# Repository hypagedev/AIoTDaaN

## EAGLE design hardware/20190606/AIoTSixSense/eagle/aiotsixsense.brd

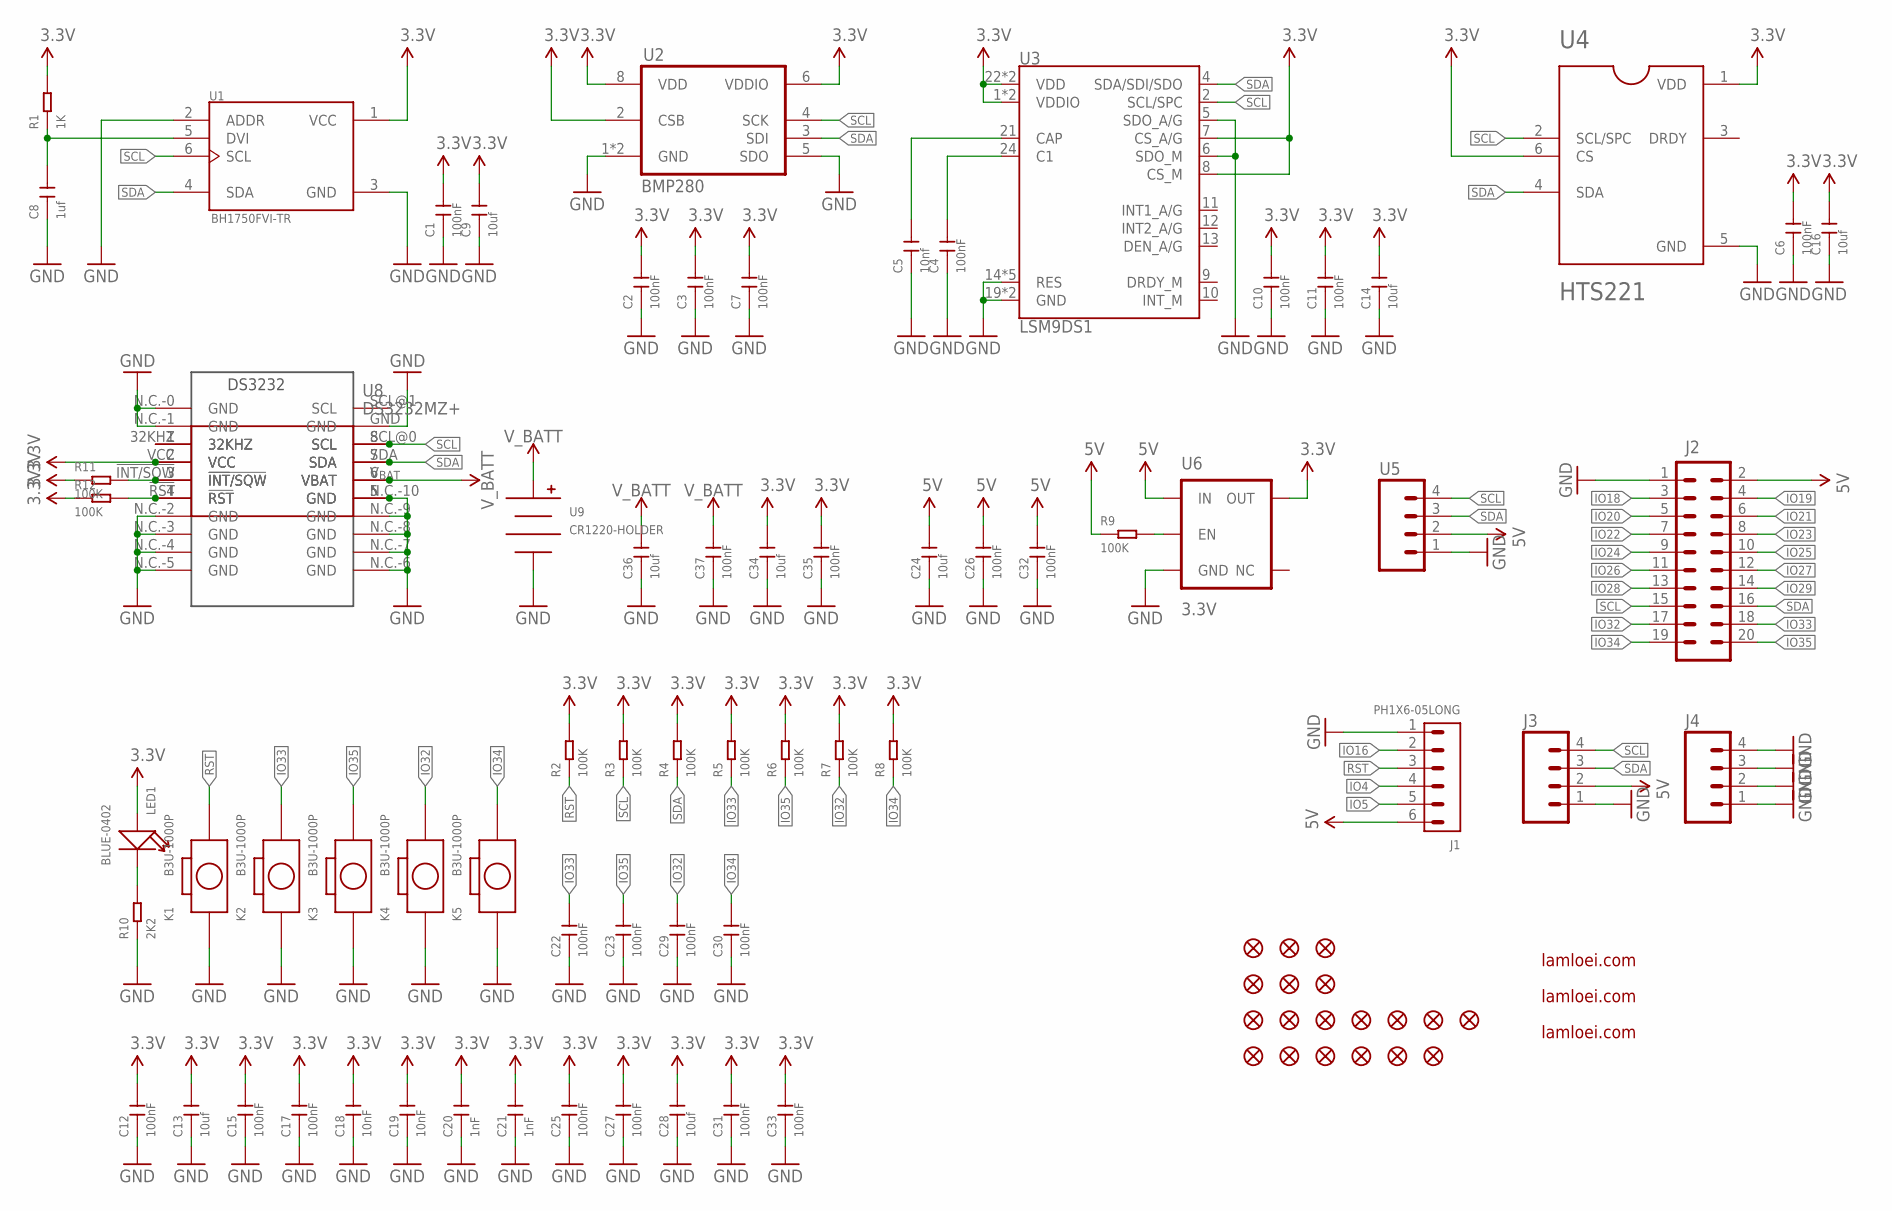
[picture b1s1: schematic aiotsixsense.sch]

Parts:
C1, C2, C3, C4, C6, C7, C10, C11, C12, C15, C17, C22, C23, C25, C26, C27, C29, C30, C31, C32, C33, C35, C37: 100nF; C0402
C5: 10nf; C0402
C8: 1uf; C0402
C9, C13, C14, C16, C24, C28, C34, C36: 10uf; C0805
C18, C19: 10nF; C0402
C20, C21: 1nF; C0402
J1: PH1X6-05LONG; PHL005-1-6
J2: M10X2; 2X10
J3, J4: M04SMD_RA_FEMALE; 1X04_SMD_RA_FEMALE
K1, K2, K3, K4, K5: B3U-1000P; SW2-SMD-3.0X2.5X1.2+0.4MM
LED1: BLUE-0402; LED-0402
R1: 1K; R0402
R2, R3, R4, R5, R6, R7, R8, R9, R11, R12: 100K; R0402
R10: 2K2; R0402
U1: BH1750FVI-TR; SOTFL50P300X75-6N
U2: BMP280
U3: LSM9DS1; LGA-24-3.5X3
U4: HTS221; LGA6R75P3X2_200X200X90
U5: M04LONGPADS; 1X04_LONGPADS
U6: 3.3V; SOT23-5
U7: DS3232; SO20-2
U8: DS3232MZ+; SOIC127P600X175-8N
U9: CR1220-HOLDER; HARWIN-CR1220
ZFCB1, ZFCB2, ZFCB3: FIDUCIAL1X2; FIDUCIAL-1X2
ZFCT1, ZFCT2, ZFCT3: FIDUCIAL1X2; FIDUCIAL-1X2
ZFDB1, ZFDB2, ZFDB3, ZFDB4, ZFDB5, ZFDB6: FIDUCIAL1X2; FIDUCIAL-1X2
ZFDT1, ZFDT2, ZFDT3, ZFDT4, ZFDT5, ZFDT6, ZFDT7: FIDUCIAL1X2; FIDUCIAL-1X2
ZL1: LAMLOEI_BIGLOGO
ZL2, ZL3: LAMLEOI_LOGO_3

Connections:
3.3V: C1.2, C2.2, C3.2, C6.2, C7.2, C9.2, C10.2, C11.2, C12.2, C13.2, C14.2, C15.2, C16.2, C17.2, C18.2, C19.2, C20.2, C21.2, C25.2, C27.2, C28.2, C31.2, C33.2, C34.2, C35.2, LED1.+, R1.2, R2.2, R3.2, R4.2, R5.2, R6.2, R7.2, R8.2, R11.1, R12.1, U1.1 (VCC), U2.2 (CSB), U2.6 (VDDIO), U2.8 (VDD), U3.1 (VDDIO), U3.3 (VDDIO), U3.7 (CS_A/G), U3.8 (CS_M), U3.22 (VDD), U3.23 (VDD), U4.1 (VDD), U4.6 (CS), U6.5 (OUT), U7.VCC, U8.2 (VCC)
5V: C24.2, C26.2, C32.2, J1.6, J2.2, J3.2, R9.1, U5.2, U6.1 (IN)
GND: C1.1, C2.1, C3.1, C4.1, C5.1, C6.1, C7.1, C8.1, C9.1, C10.1, C11.1, C12.1, C13.1, C14.1, C15.1, C16.1, C17.1, C18.1, C19.1, C20.1, C21.1, C22.1, C23.1, C24.1, C25.1, C26.1, C27.1, C28.1, C29.1, C30.1, C31.1, C32.1, C33.1, C34.1, C35.1, C36.1, C37.1, J1.1, J2.1, J3.1, J4.1, J4.2, J4.3, J4.4, K1.1, K2.1, K3.1, K4.1, K5.1, R10.1, U1.2 (ADDR), U1.3 (GND), U2.1 (GND), U2.5 (SDO), U2.7 (GND), U3.5 (SDO_A/G), U3.6 (SDO_M), U3.14 (RES), U3.15 (RES), U3.16 (RES), U3.17 (RES), U3.18 (RES), U3.19 (GND), U3.20 (GND), U4.5 (GND), U5.1, U6.2 (GND), U7.GND, U7.N.C.-0 (GND), U7.N.C.-1 (GND), U7.N.C.-2 (GND), U7.N.C.-3 (GND), U7.N.C.-4 (GND), U7.N.C.-5 (GND), U7.N.C.-6 (GND), U7.N.C.-7 (GND), U7.N.C.-8 (GND), U7.N.C.-9 (GND), U7.N.C.-10 (GND), U8.5 (GND), U9.NEG
IO4: J1.4
IO5: J1.5
IO16: J1.2
IO18: J2.3
IO19: J2.4
IO20: J2.5
IO21: J2.6
IO22: J2.7
IO23: J2.8
IO24: J2.9
IO25: J2.10
IO26: J2.11
IO27: J2.12
IO28: J2.13
IO29: J2.14
IO32: C29.2, J2.17, K4.2, R7.1
IO33: C22.2, J2.18, K2.2, R5.1
IO34: C30.2, J2.19, K5.2, R8.1
IO35: C23.2, J2.20, K3.2, R6.1
unnamed: U7.32KHZ, U8.1 (32KHZ)
unnamed: R9.2, U6.3 (EN)
unnamed: C4.2, U3.24 (C1)
unnamed: R11.2, U7.!INT/SQW, U8.3 (!INT!/SQW)
unnamed: R12.2, U7.!RST (RST), U8.4 (!RST)
unnamed: LED1.-, R10.2
unnamed: C5.2, U3.21 (CAP)
unnamed: C8.2, R1.1, U1.5 (DVI)
RST: J1.3, K1.2, R2.1
SCL: J2.15, J3.4, R3.1, U1.6 (SCL), U2.4 (SCK), U3.2 (SCL/SPC), U4.2 (SCL/SPC), U5.4, U7.SCL@0 (SCL), U8.8 (SCL)
SDA: J2.16, J3.3, R4.1, U1.4 (SDA), U2.3 (SDI), U3.4 (SDA/SDI/SDO), U4.4 (SDA), U5.3, U7.SDA, U8.7 (SDA)
V_BATT: C36.2, C37.2, U7.V_{BAT} (VBAT), U8.6 (VBAT), U9.POS

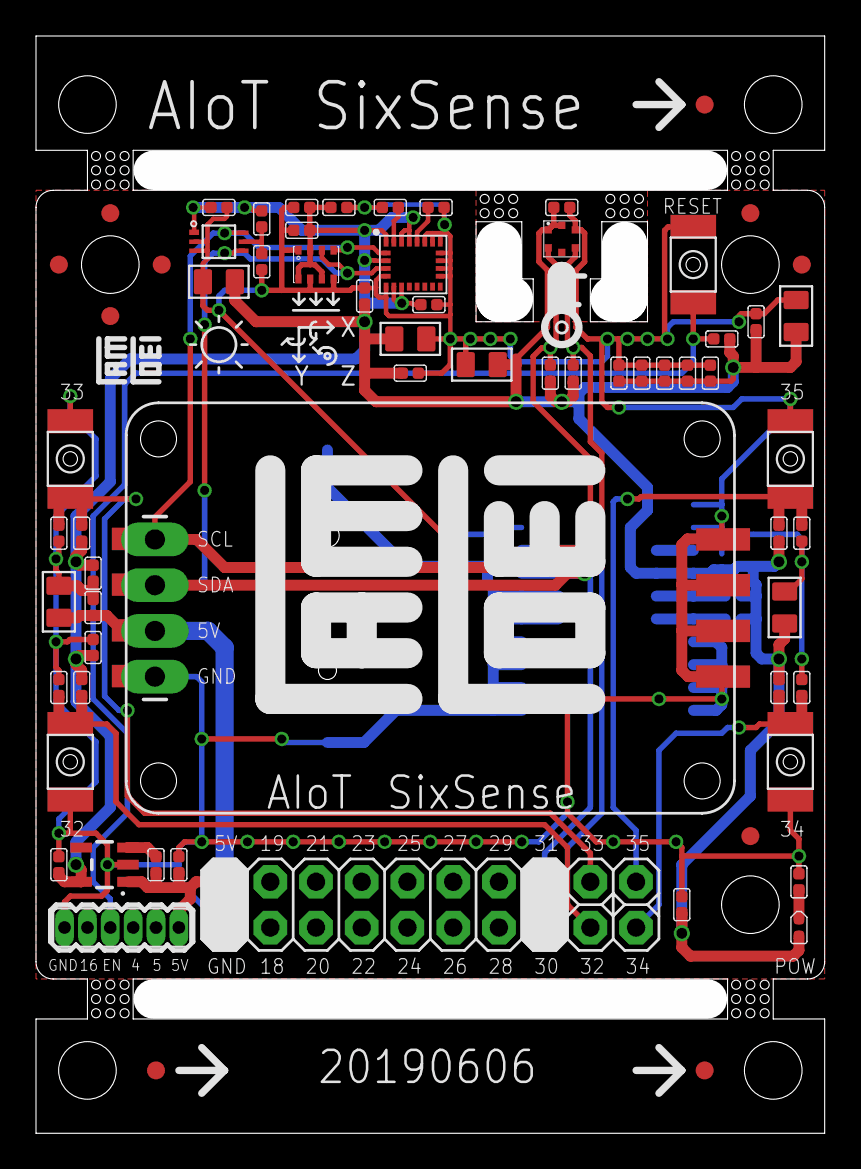
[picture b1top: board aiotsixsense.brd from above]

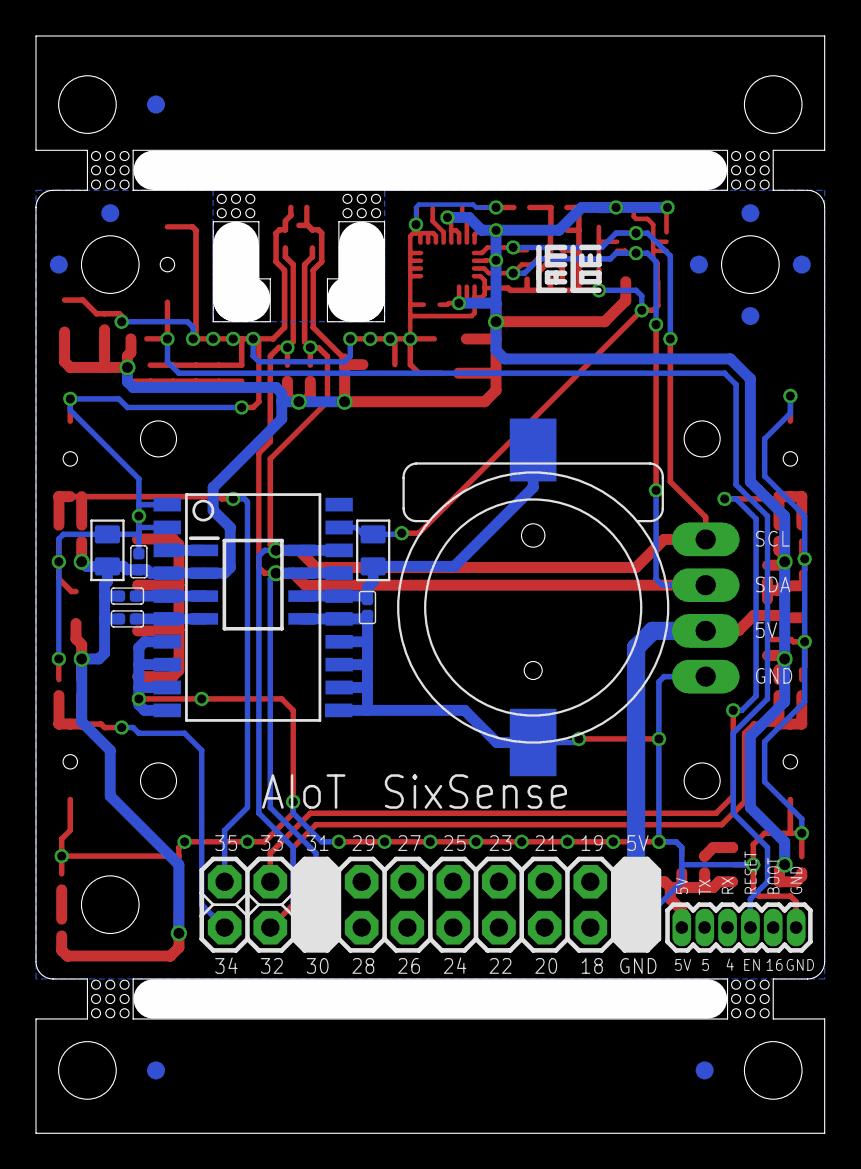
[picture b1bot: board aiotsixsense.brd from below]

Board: 2 copper layers, 43.8 x 61.0 mm, 90 parts (19 on the bottom side), 19 nets.

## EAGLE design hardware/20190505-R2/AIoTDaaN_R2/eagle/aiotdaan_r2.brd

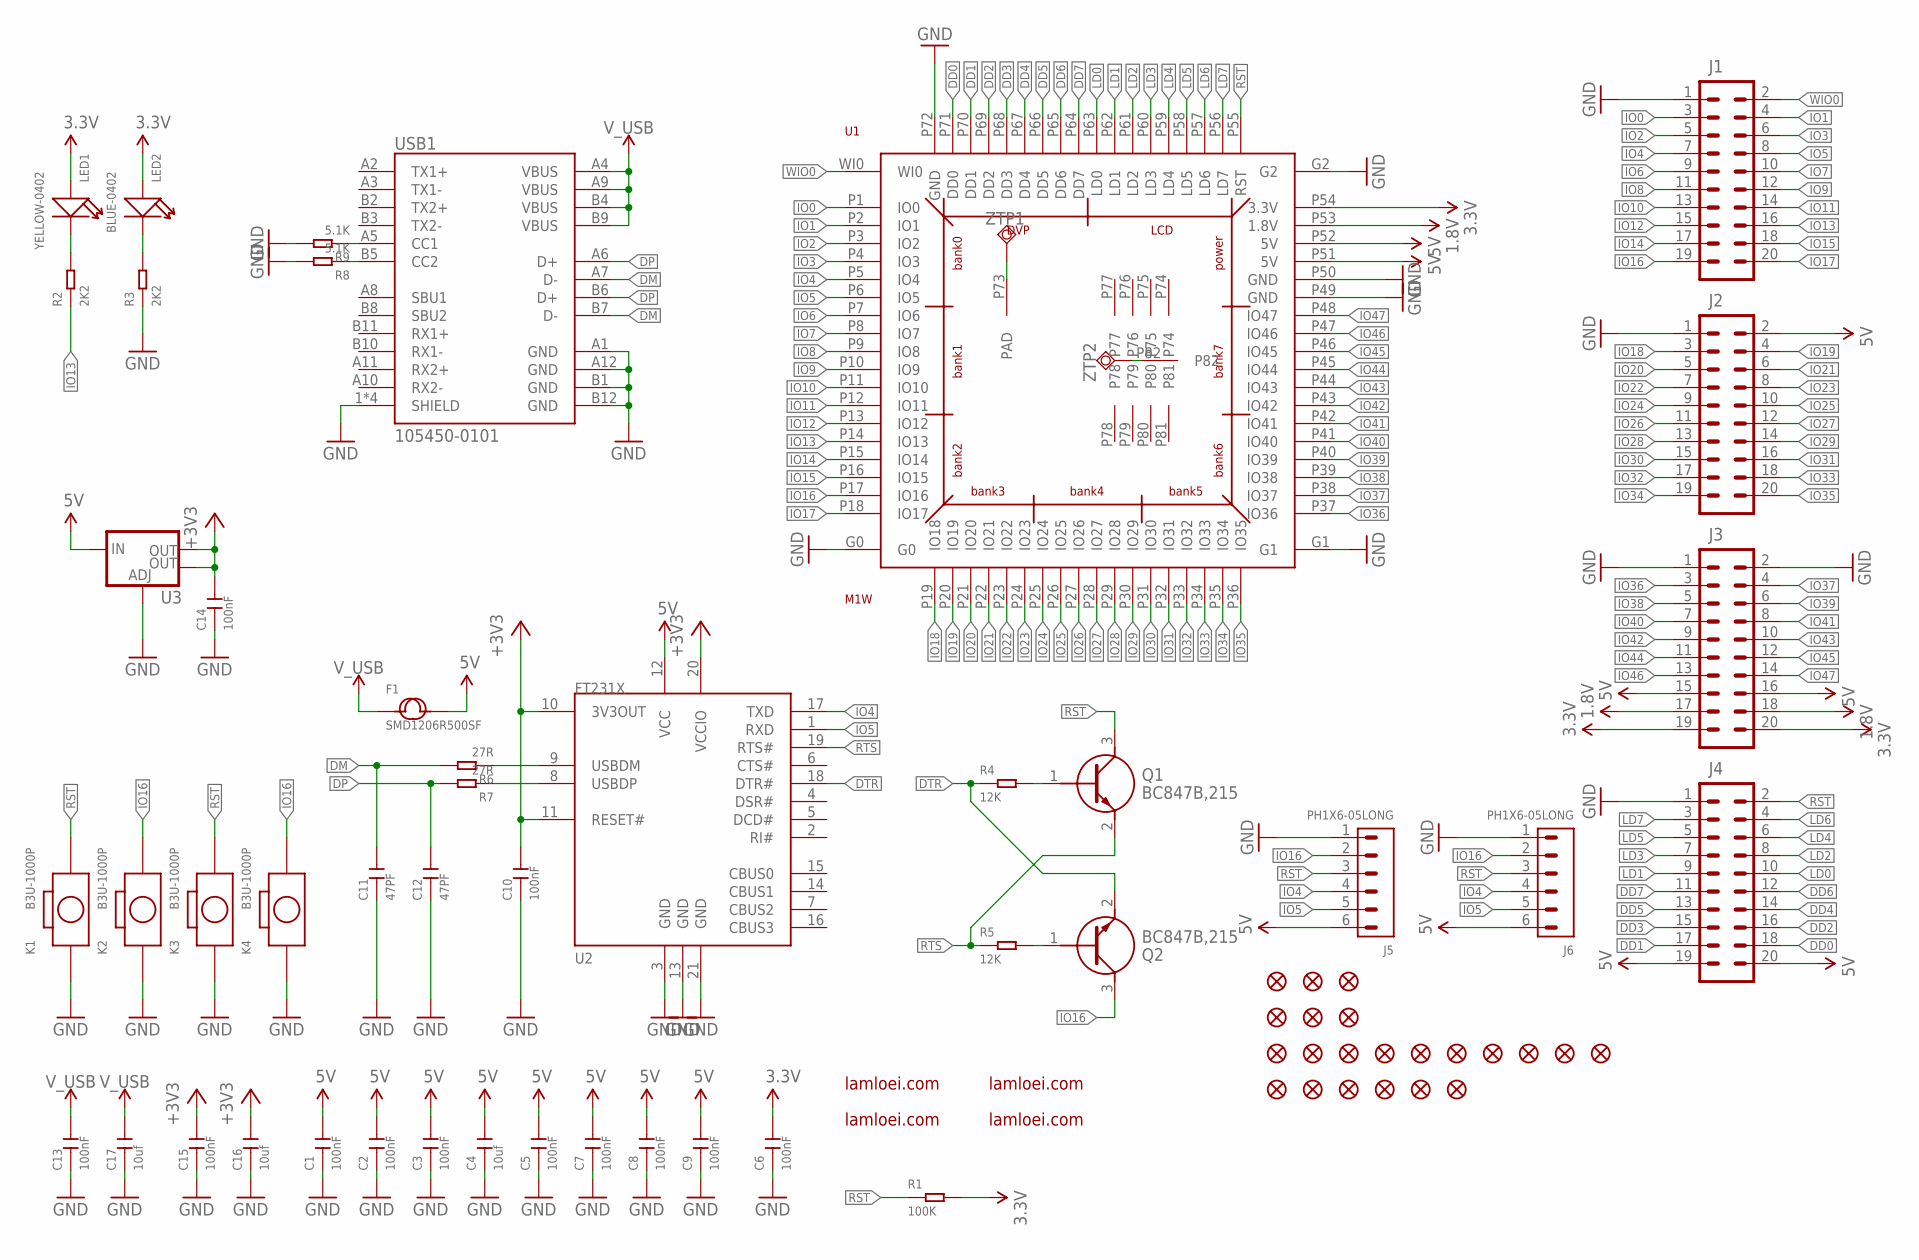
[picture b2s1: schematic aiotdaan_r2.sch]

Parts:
C1, C2, C3, C5, C6, C7, C8, C9, C10, C13, C14, C15: 100nF; C0402
C4, C16, C17: 10uf; C0805
C11, C12: 47PF; C0402
F1: SMD1206R500SF; F1206
J1, J2, J3, J4: M10X2; 2X10
J5, J6: PH1X6-05LONG; PHL005-1-6
K1, K2, K3, K4: B3U-1000P; SW2-SMD-3.0X2.5X1.2+0.4MM
LED1: YELLOW-0402; LED-0402
LED2: BLUE-0402; LED-0402
Q1, Q2: BC847B,215; SOT95P230X110-3N
R1: 100K; R0402
R2, R3: 2K2; R0402
R4, R5: 12K; R0402
R6, R7: 27R; R0402
R8, R9: 5.1K; R0402
U1: M1W
U2: FT231X-Q; QFN20
U3: V_REG_LM1117SOT223; SOT223
USB1: 105450-0101; MOLEX_105450-0101
ZFCB1, ZFCB2, ZFCB3: FIDUCIAL1X2; FIDUCIAL-1X2
ZFCT1, ZFCT2, ZFCT3: FIDUCIAL1X2; FIDUCIAL-1X2
ZFDB1, ZFDB2, ZFDB3, ZFDB4, ZFDB5, ZFDB6: FIDUCIAL1X2; FIDUCIAL-1X2
ZFDT1, ZFDT2, ZFDT3, ZFDT4, ZFDT5, ZFDT6, ZFDT7, ZFDT8, ZFDT9, ZFDT10: FIDUCIAL1X2; FIDUCIAL-1X2
ZL1, ZL2: LAMLOEI_BIGLOGO
ZL3, ZL4: LAMLEOI_LOGO_3
ZTP1, ZTP2: TPSQTP20SQ; TP20SQ

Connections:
1.8V: J3.17, J3.18, U1.P53 (1.8V)
3.3V: C6.2, J3.19, J3.20, LED1.+, LED2.+, R1.2, U1.P54 (3.3V)
5V: C1.2, C2.2, C3.2, C4.2, C5.2, C7.2, C8.2, C9.2, F1.2, J2.2, J3.15, J3.16, J4.19, J4.20, J5.6, J6.6, U1.P51 (5V), U1.P52 (5V), U2.12 (VCC), U3.3 (IN)
+3V3: C10.2, C14.2, C15.2, C16.2, U2.10 (3V3OUT), U2.11 (RESET#), U2.20 (VCCIO), U3.2 (OUT), U3.4 (OUT)
DD0: J4.18, U1.P71 (DD0)
DD1: J4.17, U1.P70 (DD1)
DD2: J4.16, U1.P69 (DD2)
DD3: J4.15, U1.P68 (DD3)
DD4: J4.14, U1.P67 (DD4)
DD5: J4.13, U1.P66 (DD5)
DD6: J4.12, U1.P65 (DD6)
DD7: J4.11, U1.P64 (DD7)
DM: C11.2, R6.2, USB1.A7 (D-), USB1.B7 (D-)
DP: C12.2, R7.2, USB1.A6 (D+), USB1.B6 (D+)
DTR: Q2.2 (E), R4.1, U2.18 (DTR#)
GND: C1.1, C2.1, C3.1, C4.1, C5.1, C6.1, C7.1, C8.1, C9.1, C10.1, C11.1, C12.1, C13.1, C14.1, C15.1, C16.1, C17.1, J1.1, J2.1, J3.1, J3.2, J4.1, J5.1, J6.1, K1.1, K2.1, K3.1, K4.1, R3.1, R8.2, R9.2, U1.G0, U1.G1, U1.G2, U1.P49 (GND), U1.P50 (GND), U1.P72 (GND), U2.3 (GND), U2.13 (GND), U2.21 (GND), U3.1 (ADJ), USB1.1 (SHIELD), USB1.2 (SHIELD), USB1.3 (SHIELD), USB1.4 (SHIELD), USB1.A1 (GND), USB1.A12 (GND), USB1.B1 (GND), USB1.B12 (GND)
IO0: J1.3, U1.P1 (IO0)
IO1: J1.4, U1.P2 (IO1)
IO2: J1.5, U1.P3 (IO2)
IO3: J1.6, U1.P4 (IO3)
IO4: J1.7, J5.4, J6.4, U1.P5 (IO4), U2.17 (TXD)
IO5: J1.8, J5.5, J6.5, U1.P6 (IO5), U2.1 (RXD)
IO6: J1.9, U1.P7 (IO6)
IO7: J1.10, U1.P8 (IO7)
IO8: J1.11, U1.P9 (IO8)
IO9: J1.12, U1.P10 (IO9)
IO10: J1.13, U1.P11 (IO10)
IO11: J1.14, U1.P12 (IO11)
IO12: J1.15, U1.P13 (IO12)
IO13: J1.16, R2.1, U1.P14 (IO13)
IO14: J1.17, U1.P15 (IO14)
IO15: J1.18, U1.P16 (IO15)
IO16: J1.19, J5.2, J6.2, K2.2, K4.2, Q2.3 (C), U1.P17 (IO16)
IO17: J1.20, U1.P18 (IO17)
IO18: J2.3, U1.P19 (IO18)
IO19: J2.4, U1.P20 (IO19)
IO20: J2.5, U1.P21 (IO20)
IO21: J2.6, U1.P22 (IO21)
IO22: J2.7, U1.P23 (IO22)
IO23: J2.8, U1.P24 (IO23)
IO24: J2.9, U1.P25 (IO24)
IO25: J2.10, U1.P26 (IO25)
IO26: J2.11, U1.P27 (IO26)
IO27: J2.12, U1.P28 (IO27)
IO28: J2.13, U1.P29 (IO28)
IO29: J2.14, U1.P30 (IO29)
IO30: J2.15, U1.P31 (IO30)
IO31: J2.16, U1.P32 (IO31)
IO32: J2.17, U1.P33 (IO32)
IO33: J2.18, U1.P34 (IO33)
IO34: J2.19, U1.P35 (IO34)
IO35: J2.20, U1.P36 (IO35)
IO36: J3.3, U1.P37 (IO36)
IO37: J3.4, U1.P38 (IO37)
IO38: J3.5, U1.P39 (IO38)
IO39: J3.6, U1.P40 (IO39)
IO40: J3.7, U1.P41 (IO40)
IO41: J3.8, U1.P42 (IO41)
IO42: J3.9, U1.P43 (IO42)
IO43: J3.10, U1.P44 (IO43)
IO44: J3.11, U1.P45 (IO44)
IO45: J3.12, U1.P46 (IO45)
IO46: J3.13, U1.P47 (IO46)
IO47: J3.14, U1.P48 (IO47)
LD0: J4.10, U1.P63 (LD0)
LD1: J4.9, U1.P62 (LD1)
LD2: J4.8, U1.P61 (LD2)
LD3: J4.7, U1.P60 (LD3)
LD4: J4.6, U1.P59 (LD4)
LD5: J4.5, U1.P58 (LD5)
LD6: J4.4, U1.P57 (LD6)
LD7: J4.3, U1.P56 (LD7)
unnamed: U1.P73 (PAD), ZTP1.TP
unnamed: U1.P82, ZTP2.TP
unnamed: LED1.-, R2.2
unnamed: R8.1, USB1.B5 (CC2)
unnamed: R9.1, USB1.A5 (CC1)
unnamed: LED2.-, R3.2
unnamed: R7.1, U2.8 (USBDP)
unnamed: R6.1, U2.9 (USBDM)
unnamed: Q2.1 (B), R5.2
unnamed: Q1.1 (B), R4.2
RST: J4.2, J5.3, J6.3, K1.2, K3.2, Q1.3 (C), R1.1, U1.P55 (RST)
RTS: Q1.2 (E), R5.1, U2.19 (RTS#)
V_USB: C13.2, C17.2, F1.1, USB1.A4 (VBUS), USB1.A9 (VBUS), USB1.B4 (VBUS), USB1.B9 (VBUS)
WIO0: J1.2, U1.WI0

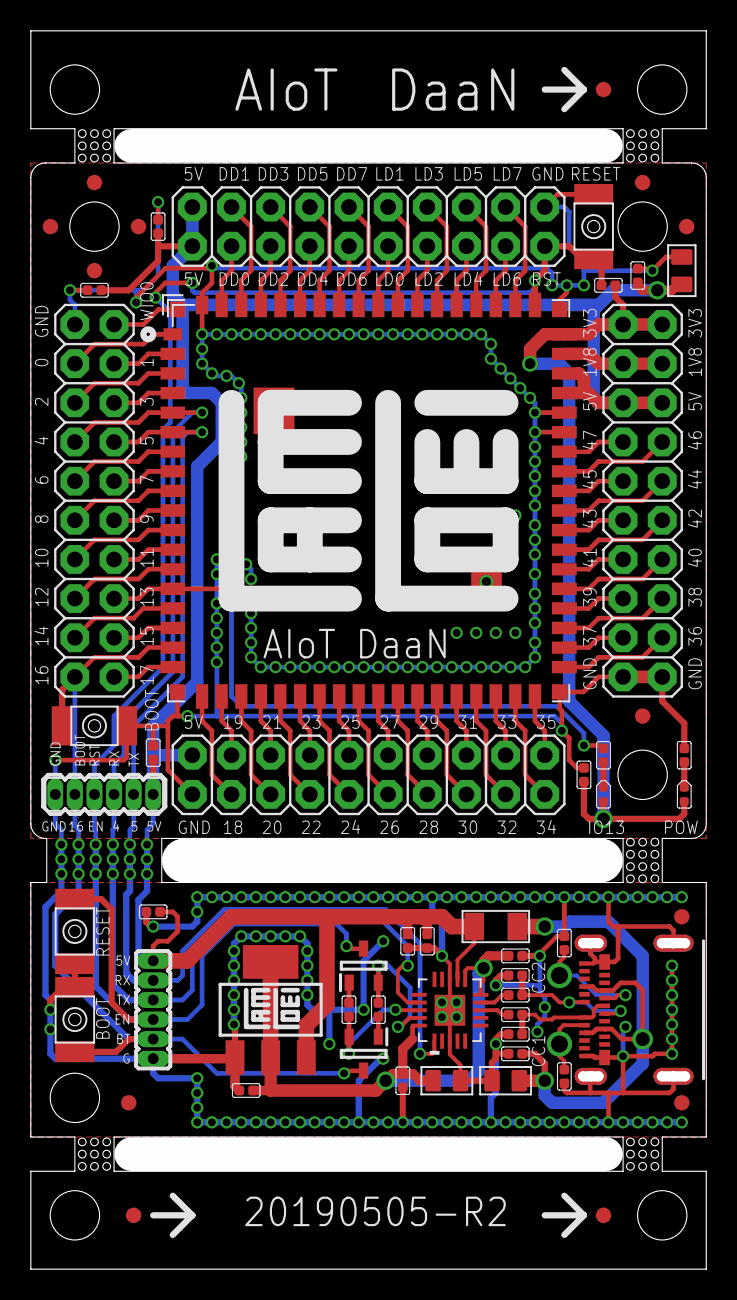
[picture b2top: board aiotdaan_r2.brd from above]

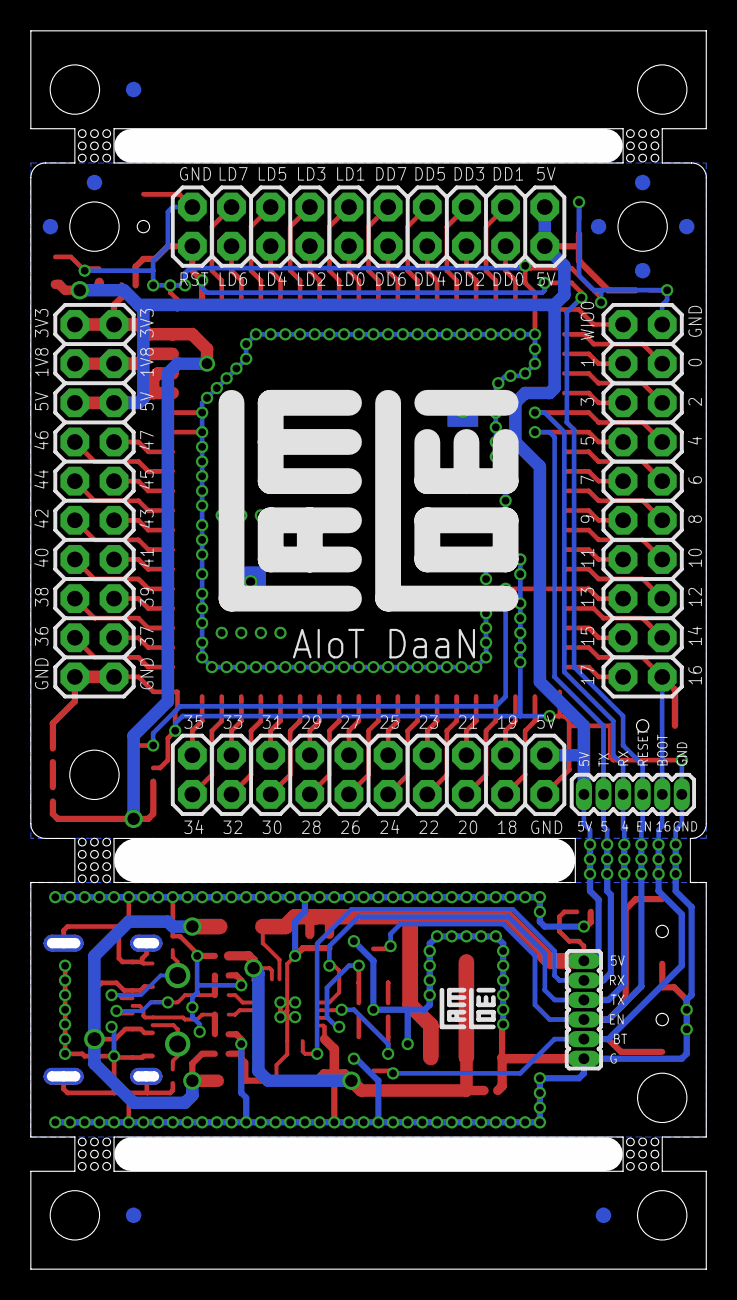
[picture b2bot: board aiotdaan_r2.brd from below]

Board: 2 copper layers, 43.8 x 80.3 mm, 73 parts (13 on the bottom side), 86 nets.

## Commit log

2019-06-17 :lollipop: Added .gitattributes & .gitignore files
2019-06-17 AIoTDaaN
    AIoTDaaN
2019-06-19 AIoTDaaN
2019-07-20 AIoT DaaN R2
2019-08-13 AIoT SixSense
    AIoT SixSense

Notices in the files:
parts and their libraries:
SparkFun-Connectors: Licensing: Creative Commons ShareAlike 4.0 International - https://creativecommons.org/licenses/by-sa/4.0
